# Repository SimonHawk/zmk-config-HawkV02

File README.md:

# HawkV0 keyboard
The HawkV02 (Hardware revision 0, firmware revision 2) is my first keyboard design. It is a 56 key fully wireless split keyboard (4x6 + 4 thumb keys for each half), made to use nice!nano microcontrollers (or clones). The PCB is flippable, so you just need two of the same PCB to have a full split keyboard.

The repository is under construction! 

## Ergogen and PCB files:
The ergogen configuration can be found in "ergogen/config_HawkV0_prod.yaml", the required footprint files in "ergogen/footprints". The ergogen output can be found in "ergogen/HawkV0_output_prod", and in the handrouted PCB can be found in "ergogen/HawkV0_output_prod/pcbs/KeyboardV0.kicad_pcb". I think the "ergogen/HawkV0_output_prod/pcbs/KeyboardV0_gerbes.zip" file should be ready to upload to a PCB manufacturer, I used jlcpcb.com with good results.

## Credit
This repository is a fork of the bug54 repository by ogruendel, because I want to start with a working ZMK configuration and modify it to my needs. Big thanks to ogruendel for making it all availible!

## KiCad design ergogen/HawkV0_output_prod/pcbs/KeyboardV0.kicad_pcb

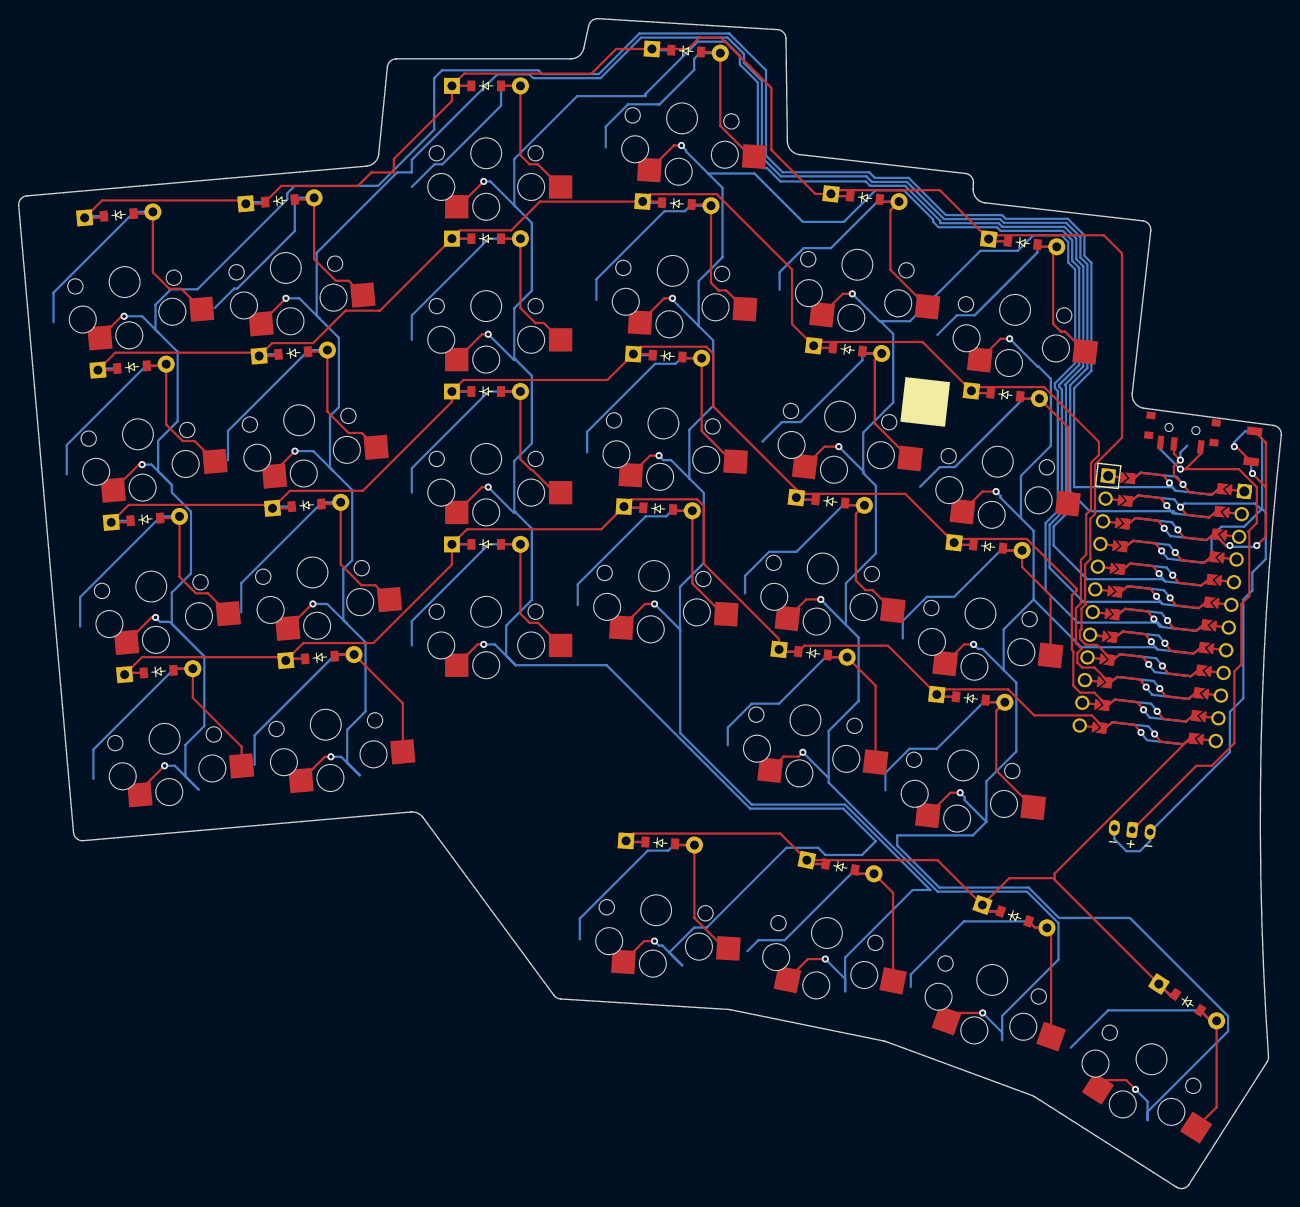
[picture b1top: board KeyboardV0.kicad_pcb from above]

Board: 2 copper layers, 140.5 x 130.1 mm, 58 parts (0 on the bottom side), 40 nets.

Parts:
D1, D2, D3, D4, D5, D6, D7, D8, D9, D10, D11, D12, D13, D14, D15, D16, D17, D18, D19, D20, D21, D22, D23, D24, D25, D26, D27, D28: ComboDiode
MCU1: ProMicro
S1, S2, S3, S4, S5, S6, S7, S8, S9, S10, S11, S12, S13, S14, S15, S16, S17, S18, S19, S20, S21, S22, S23, S24, S25, S26, S27, S28: PG1350
_3: JST_PH_S2B-PH-K_1x02_P2.00mm_Horizontal

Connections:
GND: MCU1.2, MCU1.21, MCU1.22, _3.2, _3.3
P0: MCU1.23, S5.1, S6.1, S7.1, S8.1
P1: MCU1.24, S1.1, S2.1, S3.1, S4.1
P2: MCU1.20, S9.1, S10.1, S11.1, S12.1, S25.1
P3: MCU1.19, S13.1, S14.1, S15.1, S16.1, S26.1
P4: MCU1.18, S17.1, S18.1, S19.1, S20.1, S27.1
P5: MCU1.17, S21.1, S22.1, S23.1, S24.1, S28.1
P6: D4.1, D8.1, D12.1, D16.1, D20.1, D24.1, MCU1.16
P7: D3.1, D7.1, D11.1, D15.1, D19.1, D23.1, MCU1.15
P8: D2.1, D6.1, D10.1, D14.1, D18.1, D22.1, MCU1.14
P9: D1.1, D5.1, D9.1, D13.1, D17.1, D21.1, MCU1.13
P10: D25.1, D26.1, D27.1, D28.1, MCU1.12
center_cluster: D27.2, S27.2
index_bottom: D17.2, S17.2
index_home: D18.2, S18.2
index_num: D20.2, S20.2
index_top: D19.2, S19.2
inner_bottom: D21.2, S21.2
inner_cluster: D26.2, S26.2
inner_home: D22.2, S22.2
inner_num: D24.2, S24.2
inner_top: D23.2, S23.2
middle_bottom: D13.2, S13.2
middle_home: D14.2, S14.2
middle_num: D16.2, S16.2
middle_top: D15.2, S15.2
outer_bottom: D1.2, S1.2
outer_cluster: D28.2, S28.2
outer_home: D2.2, S2.2
outer_num: D4.2, S4.2
outer_top: D3.2, S3.2
pinky_bottom: D5.2, S5.2
pinky_home: D6.2, S6.2
pinky_num: D8.2, S8.2
pinky_top: D7.2, S7.2
ring_bottom: D9.2, S9.2
ring_home: D10.2, S10.2
ring_num: D12.2, S12.2
ring_top: D11.2, S11.2
tuck_cluster: D25.2, S25.2

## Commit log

2025-06-04 First commit to see if the firmware builds
2025-06-04 Renamed all files, see if firmware still builds
2025-06-04 Fixed mistake in build.yaml, see if the firmware builds when renaming files and all mentions of bug54 to HawkV02
2025-06-04 Changed keymap and GPIO pins to actual HawkV0 specification, see if firmware still builds
2025-06-04 Ipdated layout of keymap file
2025-06-04 Added ergogen and PCB files
2025-06-07 Trying to fix connectivity issues
2025-06-07 Try again
2025-06-07 Try again2
2025-06-07 Fixed keymap error, try again
2025-06-07 Keymap issues 3
2025-06-07 Try usb logging again
